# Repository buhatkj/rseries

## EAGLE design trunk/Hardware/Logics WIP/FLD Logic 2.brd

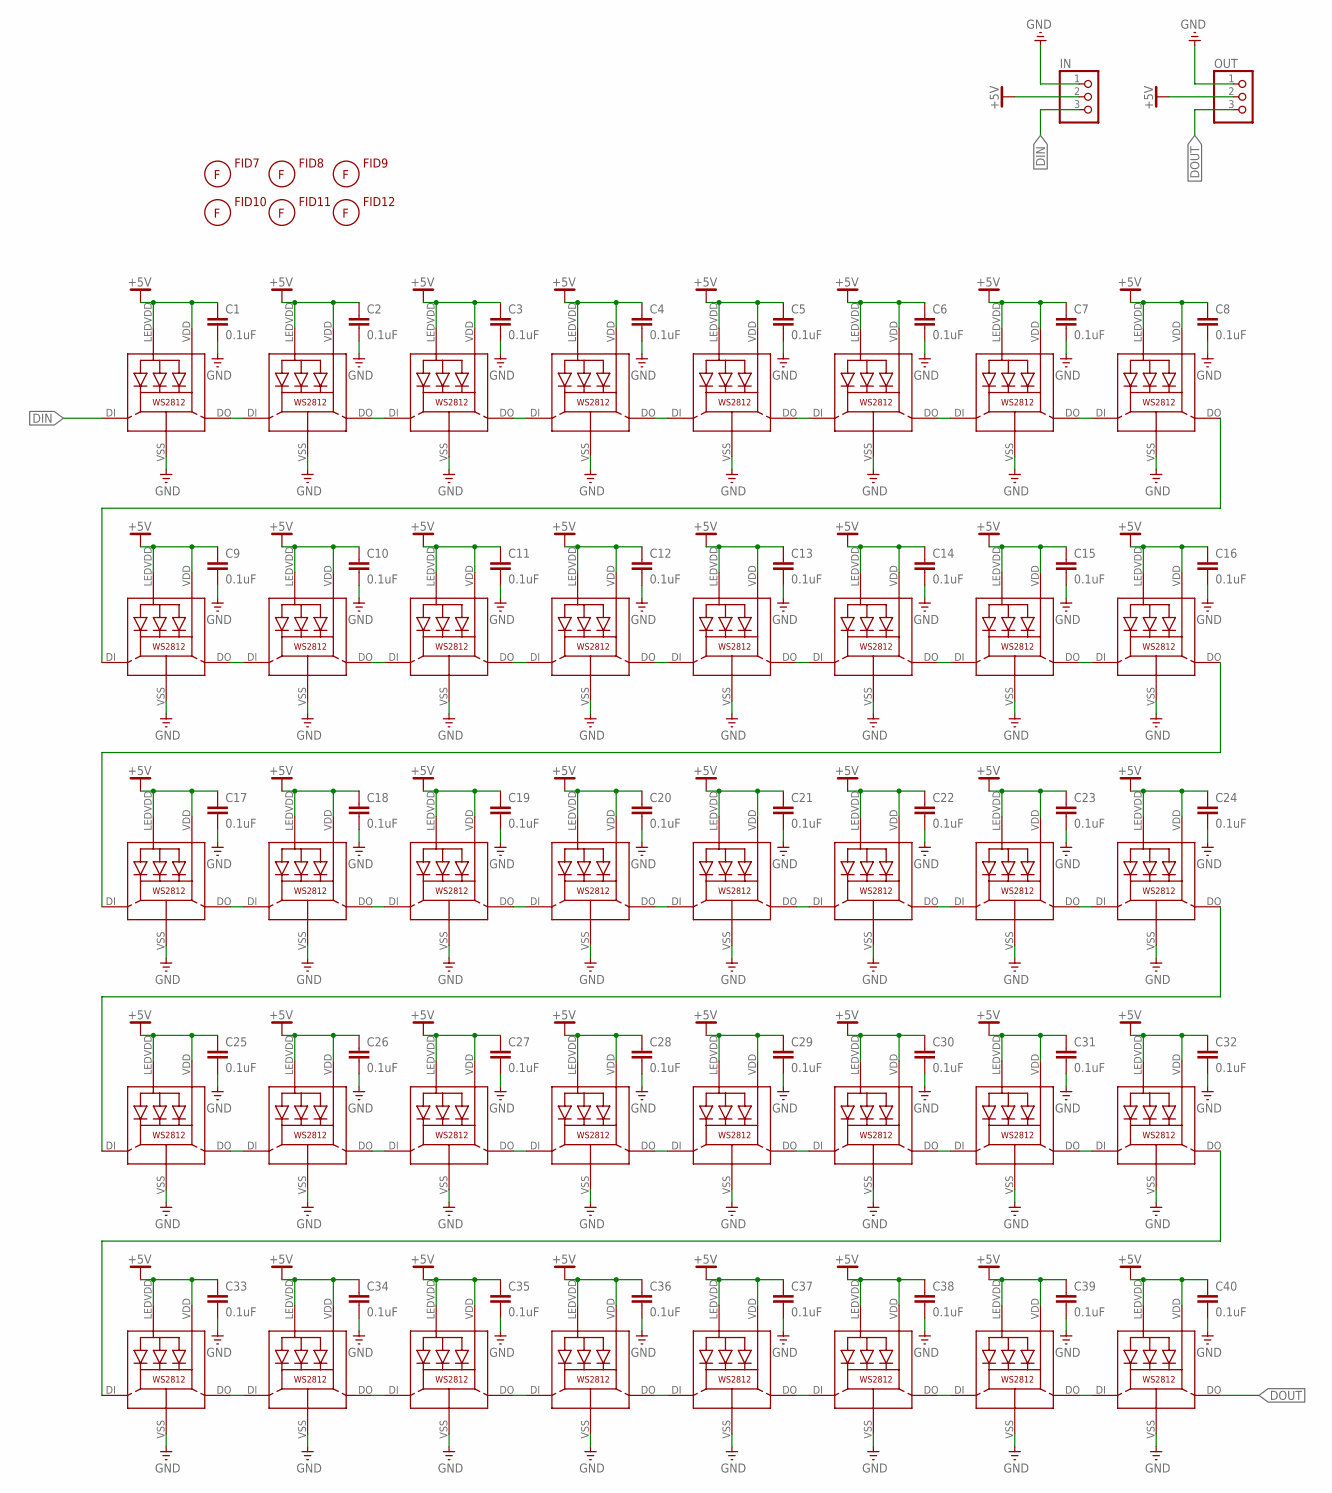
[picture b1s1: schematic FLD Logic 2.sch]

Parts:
C1, C2, C3, C4, C5, C6, C7, C8, C9, C10, C11, C12, C13, C14, C15, C16, C17, C18, C19, C20, C21, C22, C23, C24, C25, C26, C27, C28, C29, C30, C31, C32, C33, C34, C35, C36, C37, C38, C39, C40: 0.1uF; 0805
FID7, FID8, FID9, FID10, FID11, FID12: FIDUCIAL; FIDUCIAL_G15
IN: PINHD-1X3; 1X03
LED1, LED2, LED3, LED4, LED5, LED6, LED7, LED8, LED9, LED10, LED11, LED12, LED13, LED14, LED15, LED16, LED17, LED18, LED19, LED20, LED21, LED22, LED23, LED24, LED25, LED26, LED27, LED28, LED29, LED30, LED31, LED32, LED33, LED34, LED35, LED36, LED37, LED38, LED39, LED40: WS2812
OUT: PINHD-1X3; 1X03

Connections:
+5V: C1.1, C2.1, C3.1, C4.1, C5.1, C6.1, C7.1, C8.1, C9.1, C10.1, C11.1, C12.1, C13.1, C14.1, C15.1, C16.1, C17.1, C18.1, C19.1, C20.1, C21.1, C22.1, C23.1, C24.1, C25.1, C26.1, C27.1, C28.1, C29.1, C30.1, C31.1, C32.1, C33.1, C34.1, C35.1, C36.1, C37.1, C38.1, C39.1, C40.1, IN.2, LED1.LEDVDD, LED1.VDD, LED2.LEDVDD, LED2.VDD, LED3.LEDVDD, LED3.VDD, LED4.LEDVDD, LED4.VDD, LED5.LEDVDD, LED5.VDD, LED6.LEDVDD, LED6.VDD, LED7.LEDVDD, LED7.VDD, LED8.LEDVDD, LED8.VDD, LED9.LEDVDD, LED9.VDD, LED10.LEDVDD, LED10.VDD, LED11.LEDVDD, LED11.VDD, LED12.LEDVDD, LED12.VDD, LED13.LEDVDD, LED13.VDD, LED14.LEDVDD, LED14.VDD, LED15.LEDVDD, LED15.VDD, LED16.LEDVDD, LED16.VDD, LED17.LEDVDD, LED17.VDD, LED18.LEDVDD, LED18.VDD, LED19.LEDVDD, LED19.VDD, LED20.LEDVDD, LED20.VDD, LED21.LEDVDD, LED21.VDD, LED22.LEDVDD, LED22.VDD, LED23.LEDVDD, LED23.VDD, LED24.LEDVDD, LED24.VDD, LED25.LEDVDD, LED25.VDD, LED26.LEDVDD, LED26.VDD, LED27.LEDVDD, LED27.VDD, LED28.LEDVDD, LED28.VDD, LED29.LEDVDD, LED29.VDD, LED30.LEDVDD, LED30.VDD, LED31.LEDVDD, LED31.VDD, LED32.LEDVDD, LED32.VDD, LED33.LEDVDD, LED33.VDD, LED34.LEDVDD, LED34.VDD, LED35.LEDVDD, LED35.VDD, LED36.LEDVDD, LED36.VDD, LED37.LEDVDD, LED37.VDD, LED38.LEDVDD, LED38.VDD, LED39.LEDVDD, LED39.VDD, LED40.LEDVDD, LED40.VDD, OUT.2
DIN: IN.3, LED1.DI
DOUT: LED40.DO, OUT.3
GND: C1.2, C2.2, C3.2, C4.2, C5.2, C6.2, C7.2, C8.2, C9.2, C10.2, C11.2, C12.2, C13.2, C14.2, C15.2, C16.2, C17.2, C18.2, C19.2, C20.2, C21.2, C22.2, C23.2, C24.2, C25.2, C26.2, C27.2, C28.2, C29.2, C30.2, C31.2, C32.2, C33.2, C34.2, C35.2, C36.2, C37.2, C38.2, C39.2, C40.2, IN.1, LED1.VSS (GND), LED2.VSS (GND), LED3.VSS (GND), LED4.VSS (GND), LED5.VSS (GND), LED6.VSS (GND), LED7.VSS (GND), LED8.VSS (GND), LED9.VSS (GND), LED10.VSS (GND), LED11.VSS (GND), LED12.VSS (GND), LED13.VSS (GND), LED14.VSS (GND), LED15.VSS (GND), LED16.VSS (GND), LED17.VSS (GND), LED18.VSS (GND), LED19.VSS (GND), LED20.VSS (GND), LED21.VSS (GND), LED22.VSS (GND), LED23.VSS (GND), LED24.VSS (GND), LED25.VSS (GND), LED26.VSS (GND), LED27.VSS (GND), LED28.VSS (GND), LED29.VSS (GND), LED30.VSS (GND), LED31.VSS (GND), LED32.VSS (GND), LED33.VSS (GND), LED34.VSS (GND), LED35.VSS (GND), LED36.VSS (GND), LED37.VSS (GND), LED38.VSS (GND), LED39.VSS (GND), LED40.VSS (GND), OUT.1
unnamed: LED1.DO, LED2.DI
unnamed: LED3.DO, LED4.DI
unnamed: LED2.DO, LED3.DI
unnamed: LED5.DO, LED6.DI
unnamed: LED7.DO, LED8.DI
unnamed: LED6.DO, LED7.DI
unnamed: LED4.DO, LED5.DI
unnamed: LED9.DO, LED10.DI
unnamed: LED11.DO, LED12.DI
unnamed: LED10.DO, LED11.DI
unnamed: LED13.DO, LED14.DI
unnamed: LED15.DO, LED16.DI
unnamed: LED14.DO, LED15.DI
unnamed: LED12.DO, LED13.DI
unnamed: LED17.DO, LED18.DI
unnamed: LED19.DO, LED20.DI
unnamed: LED18.DO, LED19.DI
unnamed: LED21.DO, LED22.DI
unnamed: LED23.DO, LED24.DI
unnamed: LED22.DO, LED23.DI
unnamed: LED20.DO, LED21.DI
unnamed: LED25.DO, LED26.DI
unnamed: LED27.DO, LED28.DI
unnamed: LED26.DO, LED27.DI
unnamed: LED29.DO, LED30.DI
unnamed: LED31.DO, LED32.DI
unnamed: LED30.DO, LED31.DI
unnamed: LED28.DO, LED29.DI
unnamed: LED8.DO, LED9.DI
unnamed: LED16.DO, LED17.DI
unnamed: LED24.DO, LED25.DI
unnamed: LED33.DO, LED34.DI
unnamed: LED35.DO, LED36.DI
unnamed: LED34.DO, LED35.DI
unnamed: LED37.DO, LED38.DI
unnamed: LED39.DO, LED40.DI
unnamed: LED38.DO, LED39.DI
unnamed: LED36.DO, LED37.DI
unnamed: LED32.DO, LED33.DI

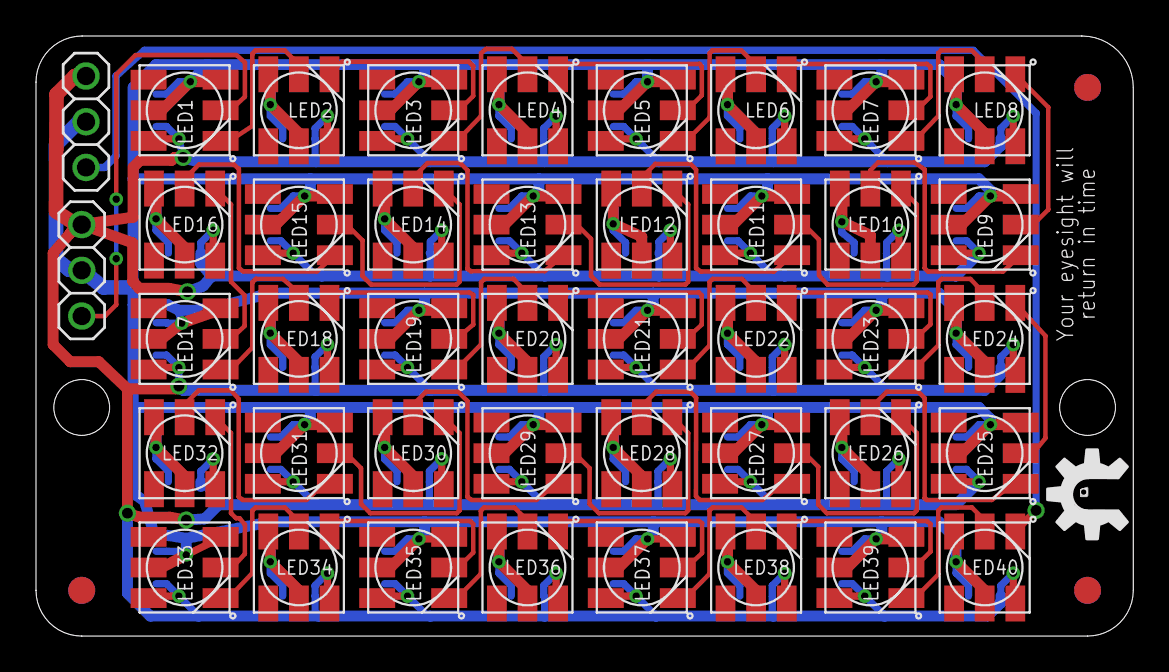
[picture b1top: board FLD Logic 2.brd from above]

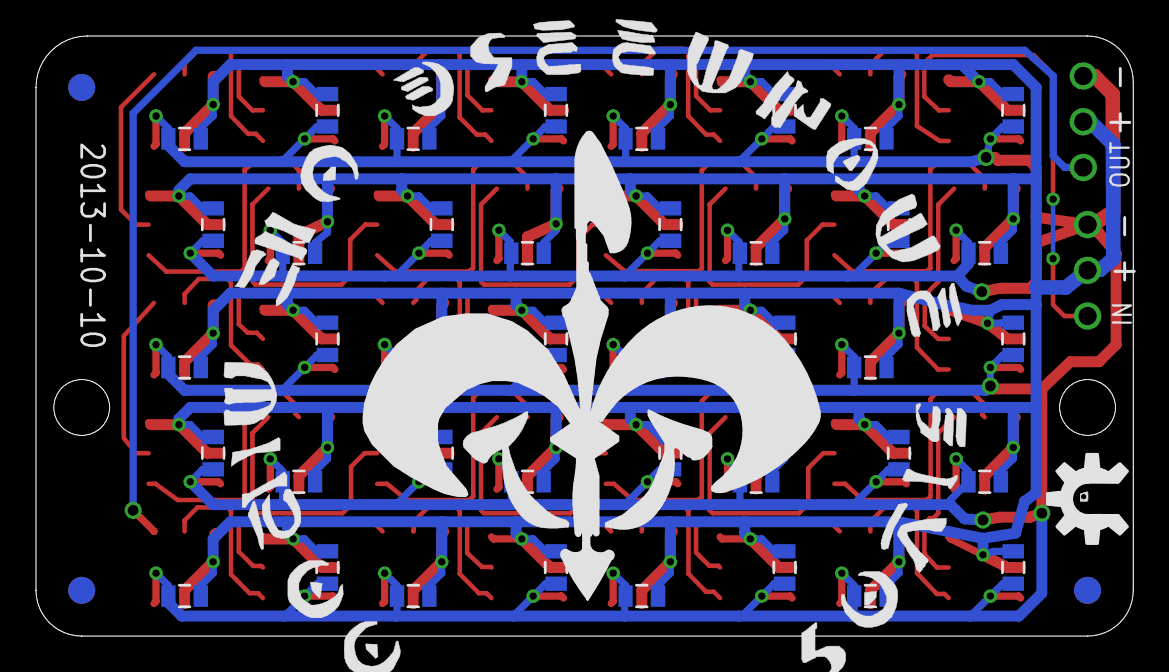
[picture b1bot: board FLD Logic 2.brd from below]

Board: 2 copper layers, 61.0 x 33.3 mm, 91 parts (44 on the bottom side), 43 nets.

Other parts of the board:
U$1: ROYAL-ENGINEERS-OF-NABOO-BOTTOM-LARGE
U$2, U$3: RSERIES-OSHW-LOGO-MEDIUM-BOTTOM

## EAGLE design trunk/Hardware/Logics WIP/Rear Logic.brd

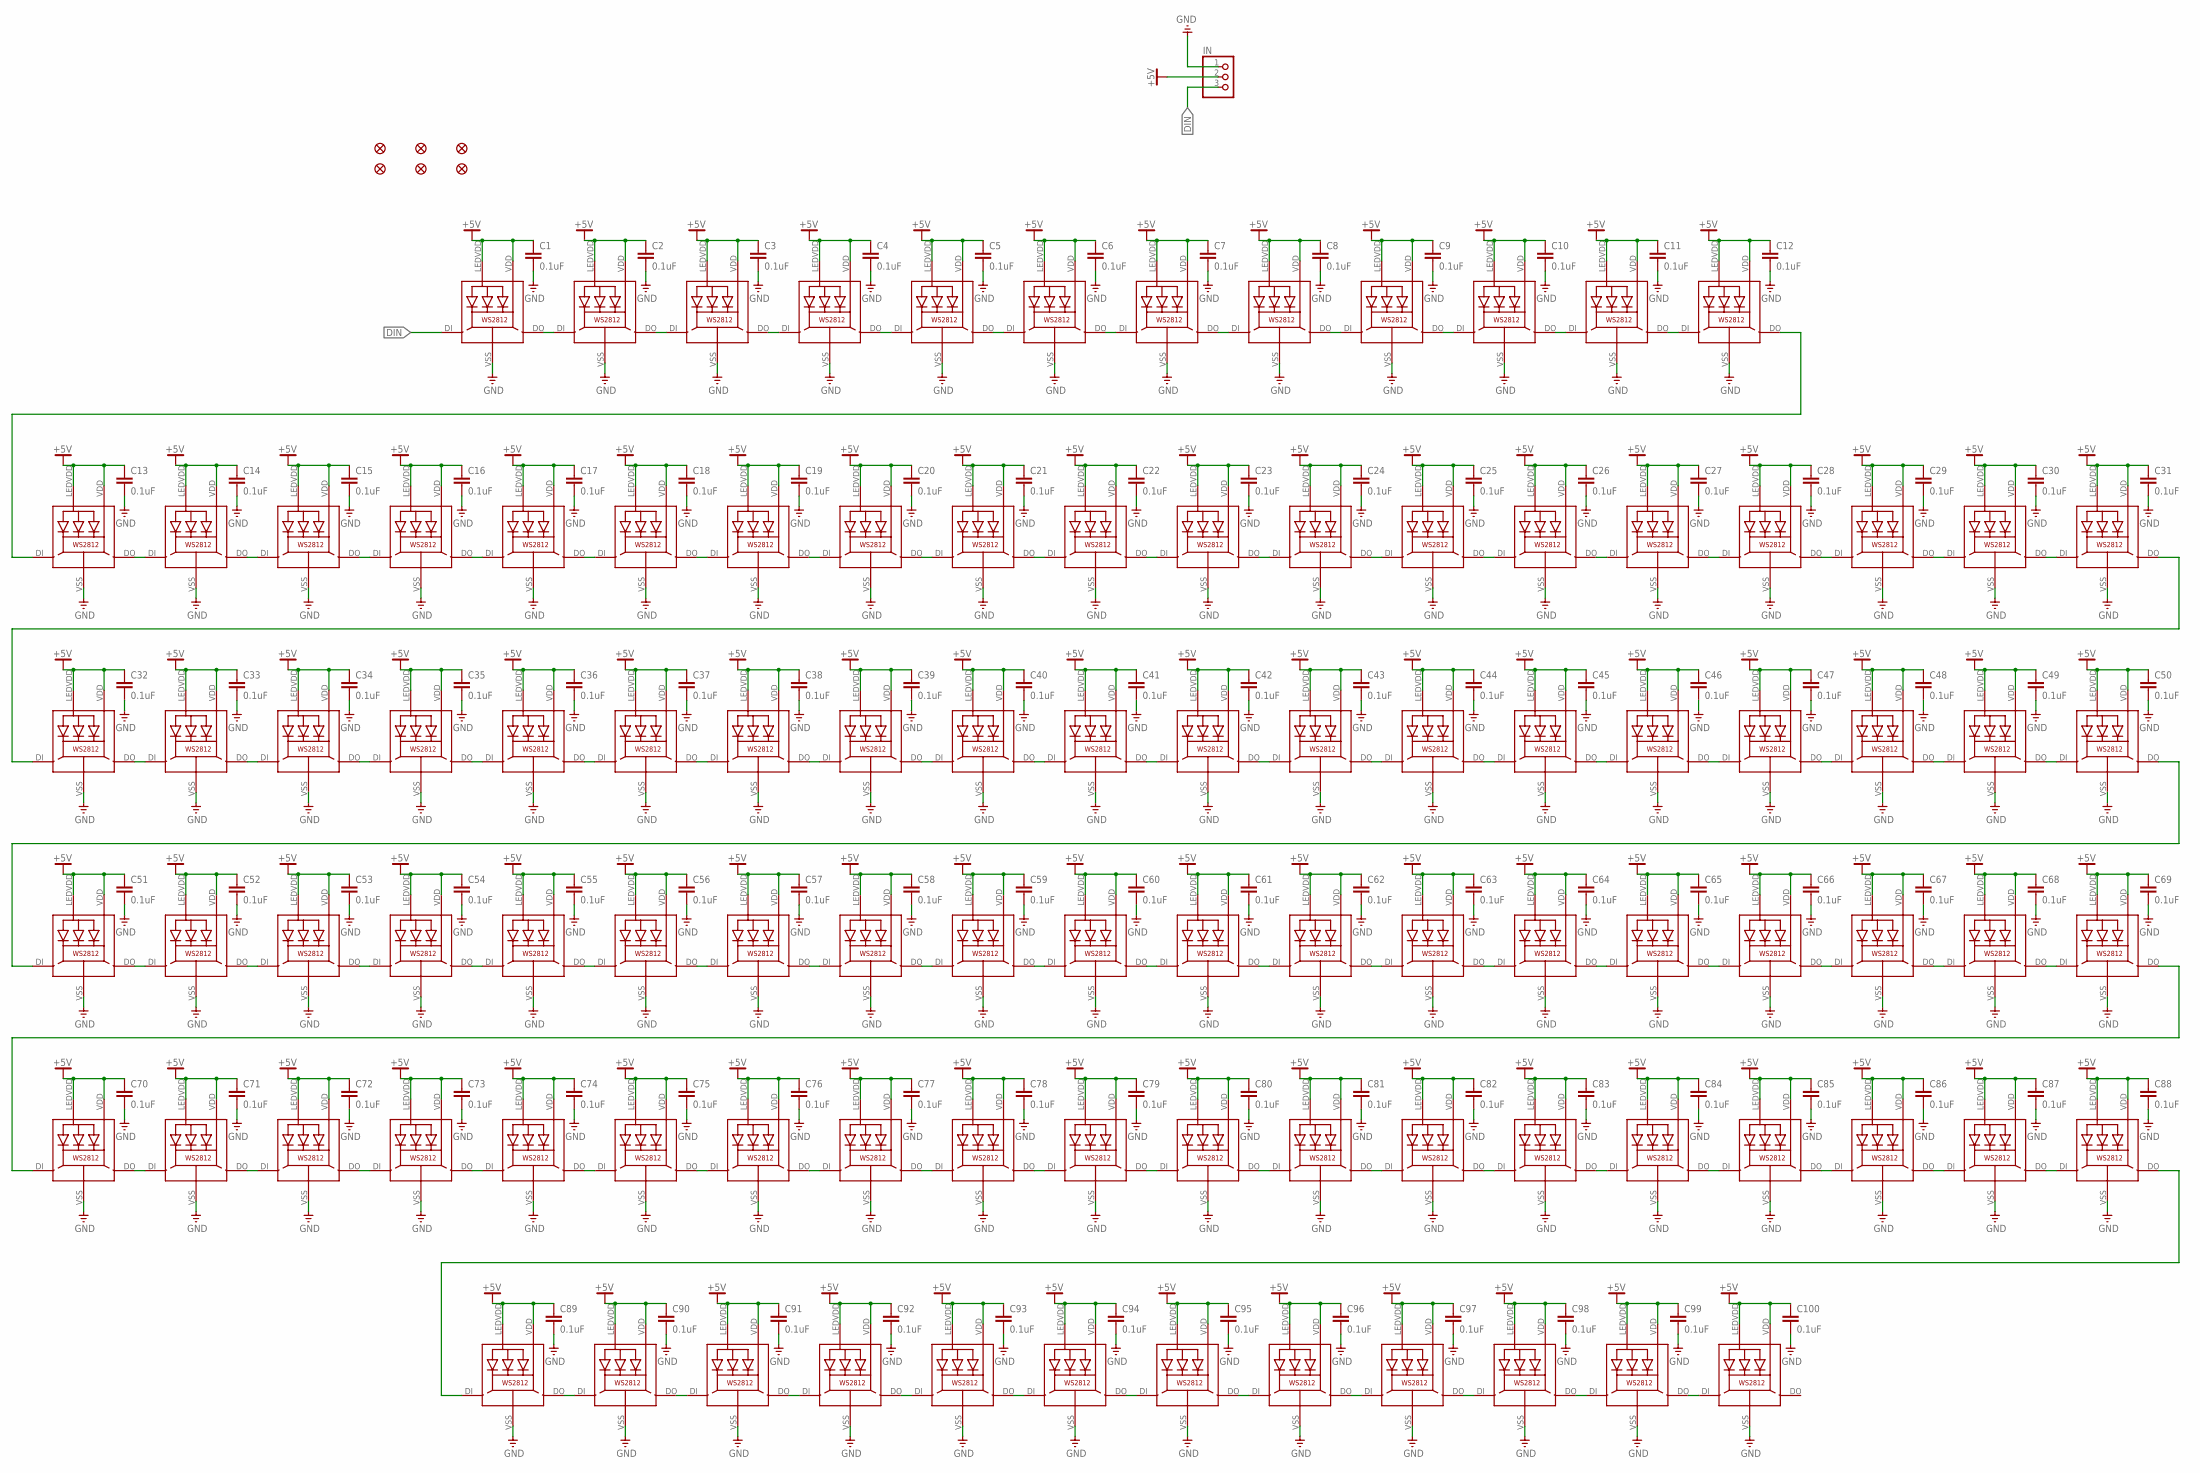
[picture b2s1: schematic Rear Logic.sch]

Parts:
C1, C2, C3, C4, C5, C6, C7, C8, C9, C10, C11, C12, C13, C14, C15, C16, C17, C18, C19, C20, C21, C22, C23, C24, C25, C26, C27, C28, C29, C30, C31, C32, C33, C34, C35, C36, C37, C38, C39, C40, C41, C42, C43, C44, C45, C46, C47, C48, C49, C50, C51, C52, C53, C54, C55, C56, C57, C58, C59, C60, C61, C62, C63, C64, C65, C66, C67, C68, C69, C70, C71, C72, C73, C74, C75, C76, C77, C78, C79, C80, C81, C82, C83, C84, C85, C86, C87, C88, C89, C90, C91, C92, C93, C94, C95, C96, C97, C98, C99, C100: 0.1uF; 0805
FID1, FID2, FID3, FID4, FID5, FID6: FIDUCIAL1.5X3; FIDUCIAL-1.5X3
IN: PINHD-1X3; 1X03
LED1, LED2, LED3, LED4, LED5, LED6, LED7, LED8, LED9, LED10, LED11, LED12, LED13, LED14, LED15, LED16, LED17, LED18, LED19, LED20, LED21, LED22, LED23, LED24, LED25, LED26, LED27, LED28, LED29, LED30, LED31, LED32, LED33, LED34, LED35, LED36, LED37, LED38, LED39, LED40, LED41, LED42, LED43, LED44, LED45, LED46, LED47, LED48, LED49, LED50, LED51, LED52, LED53, LED54, LED55, LED56, LED57, LED58, LED59, LED60, LED61, LED62, LED63, LED64, LED65, LED66, LED67, LED68, LED69, LED70, LED71, LED72, LED73, LED74, LED75, LED76, LED77, LED78, LED79, LED80, LED81, LED82, LED83, LED84, LED85, LED86, LED87, LED88, LED89, LED90, LED91, LED92, LED93, LED94, LED95, LED96, LED97, LED98, LED99, LED100: WS2812

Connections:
+5V: C1.1, C2.1, C3.1, C4.1, C5.1, C6.1, C7.1, C8.1, C9.1, C10.1, C11.1, C12.1, C13.1, C14.1, C15.1, C16.1, C17.1, C18.1, C19.1, C20.1, C21.1, C22.1, C23.1, C24.1, C25.1, C26.1, C27.1, C28.1, C29.1, C30.1, C31.1, C32.1, C33.1, C34.1, C35.1, C36.1, C37.1, C38.1, C39.1, C40.1, C41.1, C42.1, C43.1, C44.1, C45.1, C46.1, C47.1, C48.1, C49.1, C50.1, C51.1, C52.1, C53.1, C54.1, C55.1, C56.1, C57.1, C58.1, C59.1, C60.1, C61.1, C62.1, C63.1, C64.1, C65.1, C66.1, C67.1, C68.1, C69.1, C70.1, C71.1, C72.1, C73.1, C74.1, C75.1, C76.1, C77.1, C78.1, C79.1, C80.1, C81.1, C82.1, C83.1, C84.1, C85.1, C86.1, C87.1, C88.1, C89.1, C90.1, C91.1, C92.1, C93.1, C94.1, C95.1, C96.1, C97.1, C98.1, C99.1, C100.1, IN.2, LED1.LEDVDD, LED1.VDD, LED2.LEDVDD, LED2.VDD, LED3.LEDVDD, LED3.VDD, LED4.LEDVDD, LED4.VDD, LED5.LEDVDD, LED5.VDD, LED6.LEDVDD, LED6.VDD, LED7.LEDVDD, LED7.VDD, LED8.LEDVDD, LED8.VDD, LED9.LEDVDD, LED9.VDD, LED10.LEDVDD, LED10.VDD, LED11.LEDVDD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
DIN: IN.3, LED1.DI
GND: C1.2, C2.2, C3.2, C4.2, C5.2, C6.2, C7.2, C8.2, C9.2, C10.2, C11.2, C12.2, C13.2, C14.2, C15.2, C16.2, C17.2, C18.2, C19.2, C20.2, C21.2, C22.2, C23.2, C24.2, C25.2, C26.2, C27.2, C28.2, C29.2, C30.2, C31.2, C32.2, C33.2, C34.2, C35.2, C36.2, C37.2, C38.2, C39.2, C40.2, C41.2, C42.2, C43.2, C44.2, C45.2, C46.2, C47.2, C48.2, C49.2, C50.2, C51.2, C52.2, C53.2, C54.2, C55.2, C56.2, C57.2, C58.2, C59.2, C60.2, C61.2, C62.2, C63.2, C64.2, C65.2, C66.2, C67.2, C68.2, C69.2, C70.2, C71.2, C72.2, C73.2, C74.2, C75.2, C76.2, C77.2, C78.2, C79.2, C80.2, C81.2, C82.2, C83.2, C84.2, C85.2, C86.2, C87.2, C88.2, C89.2, C90.2, C91.2, C92.2, C93.2, C94.2, C95.2, C96.2, C97.2, C98.2, C99.2, C100.2, IN.1, LED1.VSS (GND), LED2.VSS (GND), LED3.VSS (GND), LED4.VSS (GND), LED5.VSS (GND), LED6.VSS (GND), LED7.VSS (GND), LED8.VSS (GND), LED9.VSS (GND), LED10.VSS (GND), LED11.VSS (GND), LED12.VSS (GND), LED13.VSS (GND), LED14.VSS (GND), LED15.VSS (GND), LED16.VSS (GND), LED17.VSS (GND), LED18.VSS (GND), LED19.VSS (GND), LED20.VSS (GND), LED21.VSS (GND)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
unnamed: LED1.DO, LED2.DI
unnamed: LED3.DO, LED4.DI
unnamed: LED2.DO, LED3.DI
unnamed: LED5.DO, LED6.DI
unnamed: LED7.DO, LED8.DI
unnamed: LED6.DO, LED7.DI
unnamed: LED4.DO, LED5.DI
unnamed: LED9.DO, LED10.DI
unnamed: LED11.DO, LED12.DI
unnamed: LED10.DO, LED11.DI
unnamed: LED8.DO, LED9.DI
unnamed: LED13.DO, LED14.DI
unnamed: LED15.DO, LED16.DI
unnamed: LED14.DO, LED15.DI
unnamed: LED17.DO, LED18.DI
unnamed: LED19.DO, LED20.DI
unnamed: LED18.DO, LED19.DI
unnamed: LED16.DO, LED17.DI
unnamed: LED21.DO, LED22.DI
unnamed: LED23.DO, LED24.DI
unnamed: LED22.DO, LED23.DI
unnamed: LED20.DO, LED21.DI
unnamed: LED26.DO, LED27.DI
unnamed: LED25.DO, LED26.DI
unnamed: LED28.DO, LED29.DI
unnamed: LED30.DO, LED31.DI
unnamed: LED29.DO, LED30.DI
unnamed: LED27.DO, LED28.DI
unnamed: LED24.DO, LED25.DI
unnamed: LED32.DO, LED33.DI
unnamed: LED34.DO, LED35.DI
unnamed: LED33.DO, LED34.DI
unnamed: LED36.DO, LED37.DI
unnamed: LED38.DO, LED39.DI
unnamed: LED37.DO, LED38.DI
unnamed: LED35.DO, LED36.DI
unnamed: LED40.DO, LED41.DI
unnamed: LED42.DO, LED43.DI
unnamed: LED41.DO, LED42.DI
unnamed: LED39.DO, LED40.DI
unnamed: LED45.DO, LED46.DI
unnamed: LED44.DO, LED45.DI
unnamed: LED47.DO, LED48.DI
unnamed: LED49.DO, LED50.DI
unnamed: LED48.DO, LED49.DI
unnamed: LED46.DO, LED47.DI
unnamed: LED43.DO, LED44.DI
unnamed: LED51.DO, LED52.DI
unnamed: LED53.DO, LED54.DI
unnamed: LED52.DO, LED53.DI
unnamed: LED55.DO, LED56.DI
unnamed: LED57.DO, LED58.DI
unnamed: LED56.DO, LED57.DI
unnamed: LED54.DO, LED55.DI
unnamed: LED59.DO, LED60.DI
unnamed: LED61.DO, LED62.DI
unnamed: LED60.DO, LED61.DI
unnamed: LED58.DO, LED59.DI
unnamed: LED64.DO, LED65.DI
unnamed: LED63.DO, LED64.DI
unnamed: LED66.DO, LED67.DI
unnamed: LED68.DO, LED69.DI
unnamed: LED67.DO, LED68.DI
unnamed: LED65.DO, LED66.DI
unnamed: LED62.DO, LED63.DI
unnamed: LED70.DO, LED71.DI
unnamed: LED72.DO, LED73.DI
unnamed: LED71.DO, LED72.DI
unnamed: LED74.DO, LED75.DI
unnamed: LED76.DO, LED77.DI
unnamed: LED75.DO, LED76.DI
unnamed: LED73.DO, LED74.DI
unnamed: LED78.DO, LED79.DI
unnamed: LED80.DO, LED81.DI
unnamed: LED79.DO, LED80.DI
unnamed: LED77.DO, LED78.DI
unnamed: LED83.DO, LED84.DI
unnamed: LED82.DO, LED83.DI
unnamed: LED85.DO, LED86.DI
unnamed: LED87.DO, LED88.DI
unnamed: LED86.DO, LED87.DI
unnamed: LED84.DO, LED85.DI
unnamed: LED81.DO, LED82.DI
unnamed: LED89.DO, LED90.DI
unnamed: LED91.DO, LED92.DI
unnamed: LED90.DO, LED91.DI
unnamed: LED93.DO, LED94.DI
unnamed: LED95.DO, LED96.DI
unnamed: LED94.DO, LED95.DI
unnamed: LED92.DO, LED93.DI
unnamed: LED97.DO, LED98.DI
unnamed: LED99.DO, LED100.DI
unnamed: LED98.DO, LED99.DI
unnamed: LED96.DO, LED97.DI
unnamed: LED12.DO, LED13.DI
unnamed: LED31.DO, LED32.DI
unnamed: LED50.DO, LED51.DI
unnamed: LED69.DO, LED70.DI
unnamed: LED88.DO, LED89.DI

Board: 2 copper layers, 207 parts (103 on the bottom side), 102 nets, no tracks yet.

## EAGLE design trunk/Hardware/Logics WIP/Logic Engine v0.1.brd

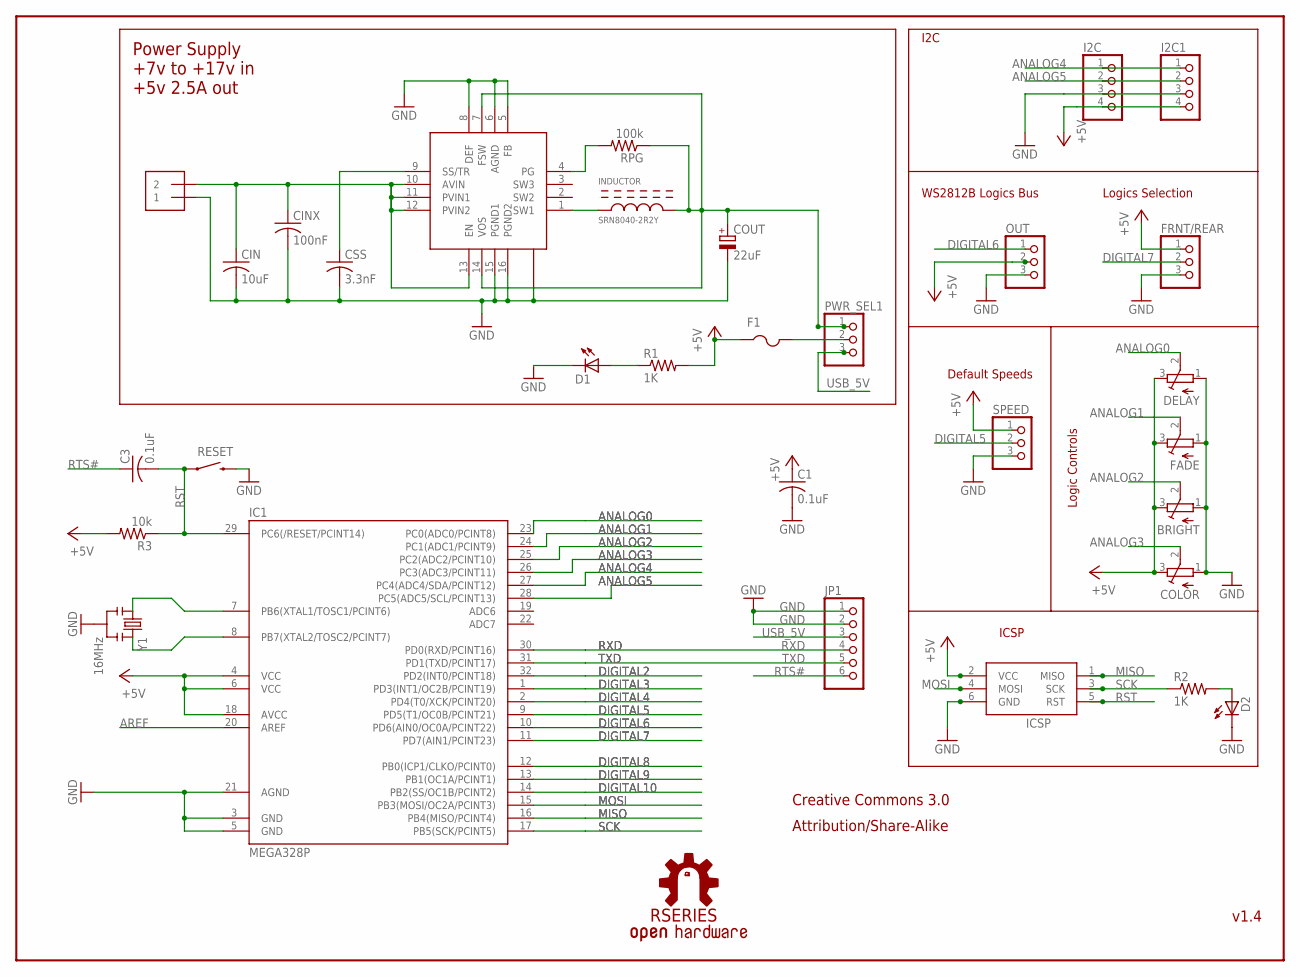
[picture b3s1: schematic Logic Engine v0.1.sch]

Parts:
BRIGHT: TRIMPOT3364W; 3364
C1, C3: 0.1uF; C0805K
CIN: 10uF; C1206
CINX: 100nF; C0805K
COLOR: TRIMPOT3364W; 3364
COUT: 22uF; CASE_B
CSS: 3.3nF; C0805K
D1: LEDCHIPLED_1206; CHIPLED_1206
D2: Green; CHIPLED_1206
DELAY: TRIMPOT3364W; 3364
EXT.PWR: 1X2-3.5MM
F1: PTCFUSE-1812; 1812
FADE: TRIMPOT3364W; 3364
FRNT/REAR: PINHD-1X3; 1X03
I2C, I2C1: PINHD-1X4CB; 1X04-CB
IC1: MEGA328P; TQFP32-08
ICSP: AVRISP-6; AVRISP
INDUCTOR: SRN8040-2R2Y; SRN8040
JP1: PINHD-1X6CLEAN; 1X06-CLEAN
OUT: PINHD-1X3; 1X03
PWR_SEL1: PINHD-1X3; 1X03
R1, R2: 1K; R0805
R3: 10k; R0805
REG: TPS62133; TPS6213X
RESET: SWITCH-MOMENTARY-2SMD; TACTILE_SWITCH_SMD
RPG: 100k; R0805
SPEED: PINHD-1X3; 1X03
U$2: RSERIES-OSHW-LOGOMEDIUM; RSERIES-OSHW-LOGO-MEDIUM
Y1: 16MHz; RESONATOR-SMD

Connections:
+5V: BRIGHT.3 (E), C1.1, COLOR.3 (E), DELAY.3 (E), F1.1, FADE.3 (E), FRNT/REAR.1, I2C.4, I2C1.4, IC1.4 (VCC), IC1.6 (VCC), IC1.18 (AVCC), ICSP.2 (VCC), OUT.2, R1.2, R3.2, SPEED.1; also elsewhere on the board
ANALOG0: DELAY.2 (S), IC1.23 (PC0(ADC0/PCINT8))
ANALOG1: FADE.2 (S), IC1.24 (PC1(ADC1/PCINT9))
ANALOG2: BRIGHT.2 (S), IC1.25 (PC2(ADC2/PCINT10))
ANALOG3: COLOR.2 (S), IC1.26 (PC3(ADC3/PCINT11))
ANALOG4: I2C.1, I2C1.1, IC1.27 (PC4(ADC4/SDA/PCINT12))
ANALOG5: I2C.2, I2C1.2, IC1.28 (PC5(ADC5/SCL/PCINT13))
AREF: IC1.20 (AREF)
DIGITAL2: IC1.32 (PD2(INT0/PCINT18))
DIGITAL3: IC1.1 (PD3(INT1/OC2B/PCINT19))
DIGITAL4: IC1.2 (PD4(T0/XCK/PCINT20))
DIGITAL5: IC1.9 (PD5(T1/OC0B/PCINT21)), SPEED.2
DIGITAL6: IC1.10 (PD6(AIN0/OC0A/PCINT22)), OUT.1
DIGITAL7: FRNT/REAR.2, IC1.11 (PD7(AIN1/PCINT23))
DIGITAL8: IC1.12 (PB0(ICP1/CLKO/PCINT0)); also elsewhere on the board
DIGITAL9: IC1.13 (PB1(OC1A/PCINT1)); also elsewhere on the board
DIGITAL10: IC1.14 (PB2(SS/OC1B/PCINT2)); also elsewhere on the board
GND: BRIGHT.1 (A), C1.2, CIN.2, CINX.2, COLOR.1 (A), COUT.-, CSS.2, D1.C, D2.C, DELAY.1 (A), EXT.PWR.1, FADE.1 (A), FRNT/REAR.3, I2C.3, I2C1.3, IC1.3 (GND), IC1.5 (GND), IC1.21 (AGND), ICSP.6 (GND), JP1.1, JP1.2, OUT.3, REG.5 (FB), REG.6 (AGND), REG.8 (DEF), REG.15 (PGND1), REG.16 (PGND2), REG.17-THERMALPAD (THERM), RESET.3 (2), SPEED.3, Y1.2; also elsewhere on the board
MISO: IC1.16 (PB4(MISO/PCINT4)), ICSP.1 (MISO)
MOSI: IC1.15 (PB3(MOSI/OC2A/PCINT3)), ICSP.4 (MOSI)
unnamed: IC1.7 (PB6(XTAL1/TOSC1/PCINT6)), Y1.1
unnamed: IC1.8 (PB7(XTAL2/TOSC2/PCINT7)), Y1.3
unnamed: INDUCTOR.P$1 (P1), REG.1 (SW1)
unnamed: D2.A, R2.2
unnamed: D1.A, R1.1
unnamed: CSS.1, REG.9 (SS/TR)
unnamed: REG.4 (PG), RPG.2
unnamed: COUT.+, INDUCTOR.P$2 (P2), PWR_SEL1.1, REG.7 (FSW), REG.14 (VOS), RPG.1
unnamed: F1.2, PWR_SEL1.2
RST: C3.2, IC1.29 (PC6(/RESET/PCINT14)), ICSP.5 (RST), R3.1, RESET.1
RTS#: C3.1, JP1.6
RXD: IC1.30 (PD0(RXD/PCINT16)), JP1.4
SCK: IC1.17 (PB5(SCK/PCINT5)), ICSP.3 (SCK), R2.1
TXD: IC1.31 (PD1(TXD/PCINT17)), JP1.5
USB_5V: JP1.3, PWR_SEL1.3

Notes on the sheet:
v1.4
Creative Commons 3.0
Attribution/Share-Alike
WS2812B Logics Bus
I2C
ICSP
Power Supply +7v to +17v in +5v 2.5A out
Logic Controls
Logics Selection
Default Speeds

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
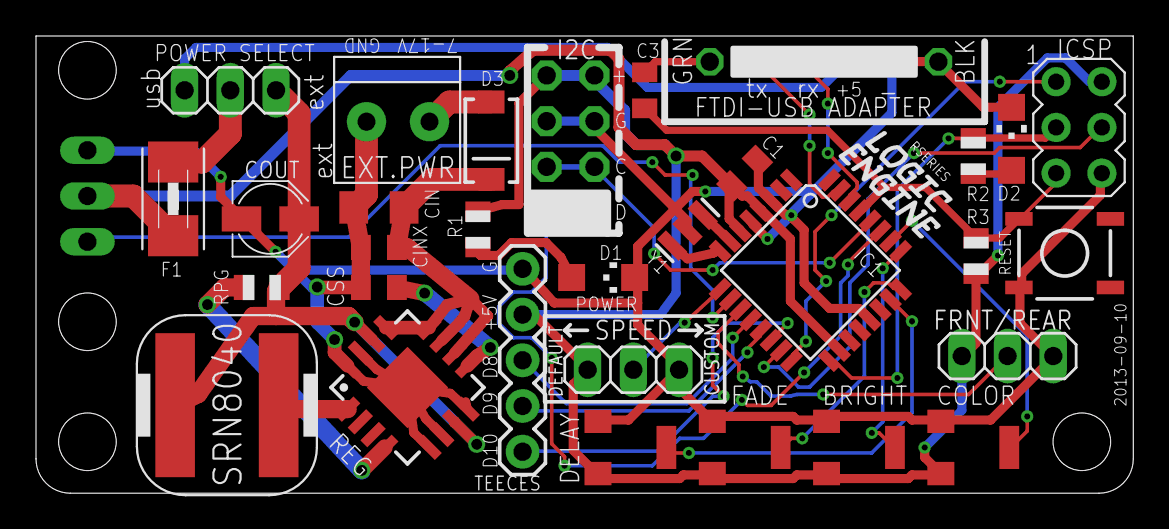
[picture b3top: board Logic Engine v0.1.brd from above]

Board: 2 copper layers, 61.0 x 25.4 mm, 33 parts (1 on the bottom side), 33 nets.

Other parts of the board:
D3: BA340LA; SMA-DIODE
TEECES: 1X05

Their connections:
+5V: TEECES.2; also elsewhere on the board
DIGITAL8: TEECES.3; also elsewhere on the board
DIGITAL9: TEECES.4; also elsewhere on the board
DIGITAL10: TEECES.5; also elsewhere on the board
GND: TEECES.1; also elsewhere on the board

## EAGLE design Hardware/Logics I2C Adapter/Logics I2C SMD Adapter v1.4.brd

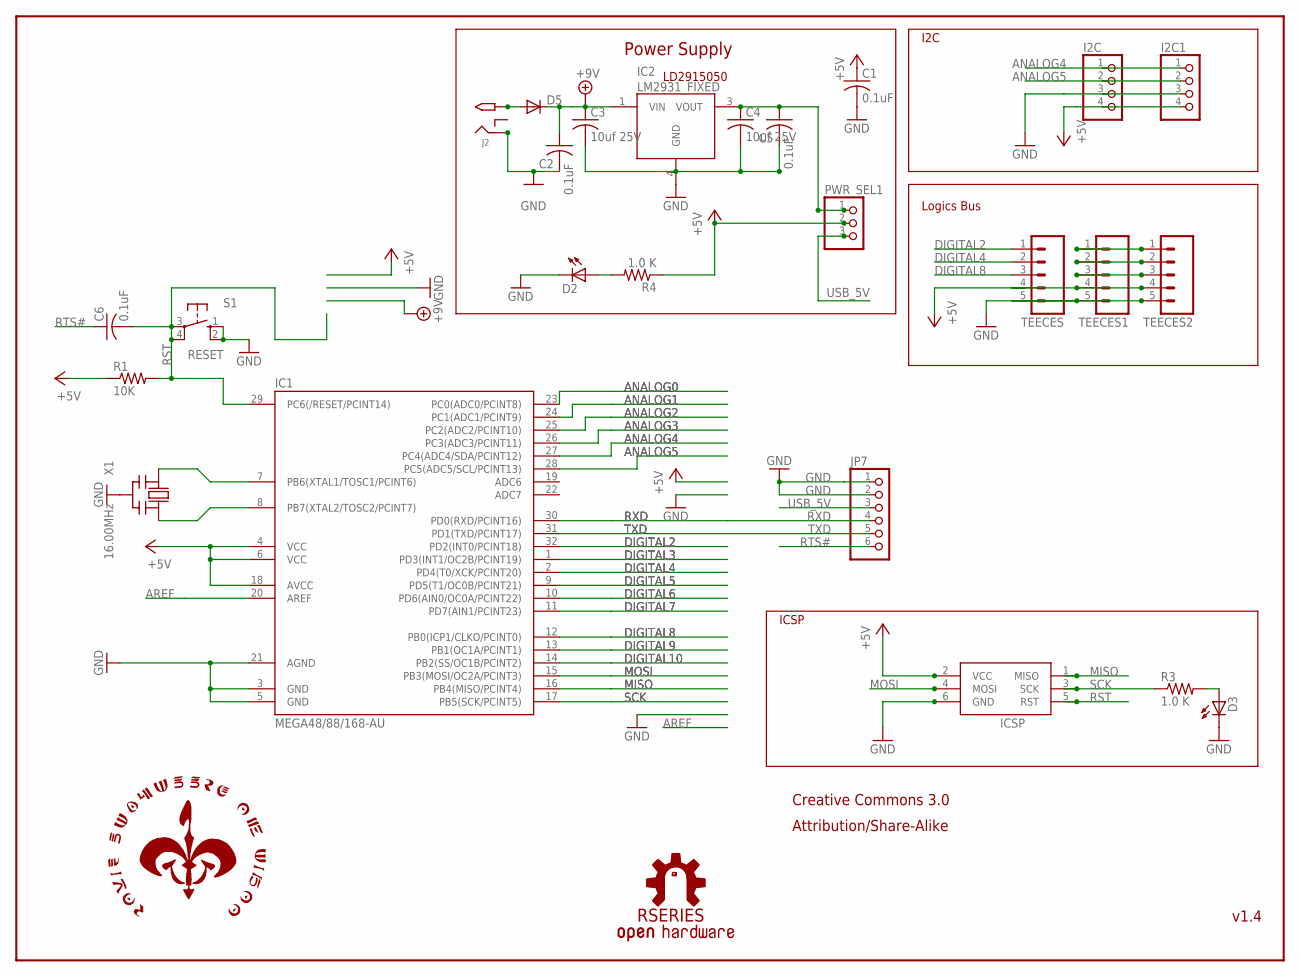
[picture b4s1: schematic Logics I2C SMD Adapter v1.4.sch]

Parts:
C1, C2, C5, C6: 0.1uF; C1206K
C3, C4: 10uf 25V; C1206K
D2: LEDCHIPLED_1206; CHIPLED_1206
D3: Green; CHIPLED_1206
D5: DIODE-SMB; SMB
I2C, I2C1: PINHD-1X4CB; 1X04-CB
IC1: MEGA48/88/168-AU; TQFP32-08
IC2: LM2931_FIXED; DPAK
ICSP: AVRISP-6; AVRISP
J2: 2.1MMJACK; PJ-102A
JP7: PINHD-1X6CLEAN; 1X06-CLEAN
PWR_SEL1: PINHD-1X3; 1X03
R1: 10K; R1206
R3, R4: 1.0 K; M1206
S1: RESET; B3F-10XX
TEECES, TEECES1, TEECES2: M05PTH; 1X05
U$1: ROYAL-ENGINEERS-OF-NABOOSMALL; ROYAL-ENGINEERS-OF-NABOO-SMALL
U$2: RSERIES-OSHW-LOGOMEDIUM; RSERIES-OSHW-LOGO-MEDIUM
X1: 16.00MHz; CERM_OSC

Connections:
+5V: C1.1, I2C.4, I2C1.4, IC1.4 (VCC), IC1.6 (VCC), IC1.18 (AVCC), ICSP.2 (VCC), PWR_SEL1.2, R1.1, R4.1, TEECES.4, TEECES1.4, TEECES2.4
+9V: C2.1, C3.1, D5.C, IC2.1 (VIN)
ANALOG0: IC1.23 (PC0(ADC0/PCINT8))
ANALOG1: IC1.24 (PC1(ADC1/PCINT9))
ANALOG2: IC1.25 (PC2(ADC2/PCINT10))
ANALOG3: IC1.26 (PC3(ADC3/PCINT11))
ANALOG4: I2C.1, I2C1.1, IC1.27 (PC4(ADC4/SDA/PCINT12))
ANALOG5: I2C.2, I2C1.2, IC1.28 (PC5(ADC5/SCL/PCINT13))
AREF: IC1.20 (AREF)
DIGITAL2: IC1.32 (PD2(INT0/PCINT18)), TEECES.1
DIGITAL3: IC1.1 (PD3(INT1/OC2B/PCINT19))
DIGITAL4: IC1.2 (PD4(T0/XCK/PCINT20)), TEECES.2
DIGITAL5: IC1.9 (PD5(T1/OC0B/PCINT21))
DIGITAL6: IC1.10 (PD6(AIN0/OC0A/PCINT22))
DIGITAL7: IC1.11 (PD7(AIN1/PCINT23))
DIGITAL8: IC1.12 (PB0(ICP1/CLKO/PCINT0)), TEECES.3
DIGITAL9: IC1.13 (PB1(OC1A/PCINT1))
DIGITAL10: IC1.14 (PB2(SS/OC1B/PCINT2))
GND: C1.2, C2.2, D2.C, D3.C, I2C.3, I2C1.3, IC1.3 (GND), IC1.5 (GND), IC1.21 (AGND), IC2.4 (GND), ICSP.6 (GND), J2.RING, JP7.1, JP7.2, S1.1 (S), S1.2 (S1), TEECES.5, TEECES1.5, TEECES2.5, X1.P$2 (GND)
MISO: IC1.16 (PB4(MISO/PCINT4)), ICSP.1 (MISO)
MOSI: IC1.15 (PB3(MOSI/OC2A/PCINT3)), ICSP.4 (MOSI)
unnamed: IC1.7 (PB6(XTAL1/TOSC1/PCINT6)), X1.P$1 (IN)
unnamed: IC1.8 (PB7(XTAL2/TOSC2/PCINT7)), X1.P$3 (OUT)
unnamed: TEECES1.3, TEECES2.3
unnamed: D3.A, R3.2
unnamed: D2.A, R4.2
unnamed: D5.A, J2.TIP
unnamed: TEECES1.2, TEECES2.2
unnamed: C3.2, C4.2, C5.2
unnamed: C4.1, C5.1, IC2.3 (VOUT), PWR_SEL1.1
unnamed: TEECES1.1, TEECES2.1
RST: C6.2, IC1.29 (PC6(/RESET/PCINT14)), ICSP.5 (RST), R1.2, S1.3, S1.4 (P1)
RTS#: C6.1, JP7.6
RXD: IC1.30 (PD0(RXD/PCINT16)), JP7.4
SCK: IC1.17 (PB5(SCK/PCINT5)), ICSP.3 (SCK), R3.1
TXD: IC1.31 (PD1(TXD/PCINT17)), JP7.5
USB_5V: JP7.3, PWR_SEL1.3

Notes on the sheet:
v1.4
Creative Commons 3.0
Attribution/Share-Alike
Logics Bus
I2C
ICSP
Power Supply
LD2915050

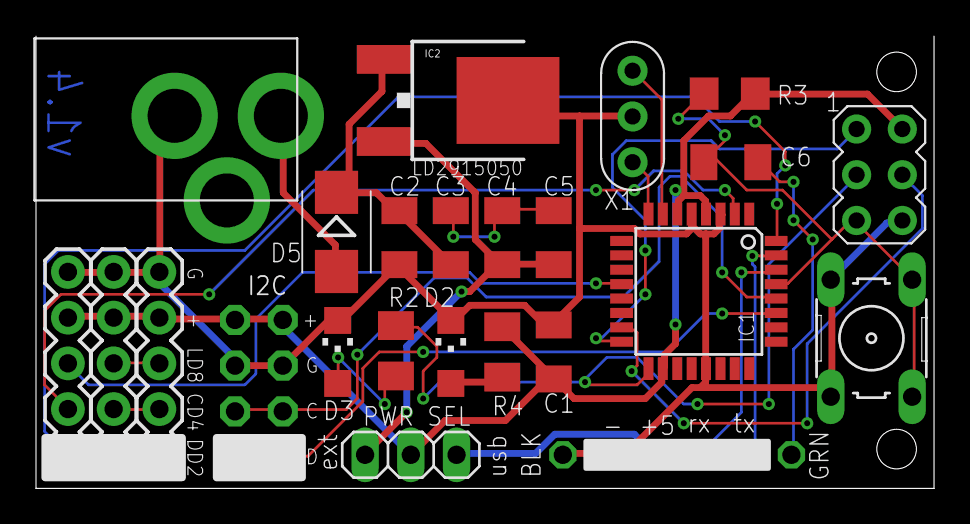
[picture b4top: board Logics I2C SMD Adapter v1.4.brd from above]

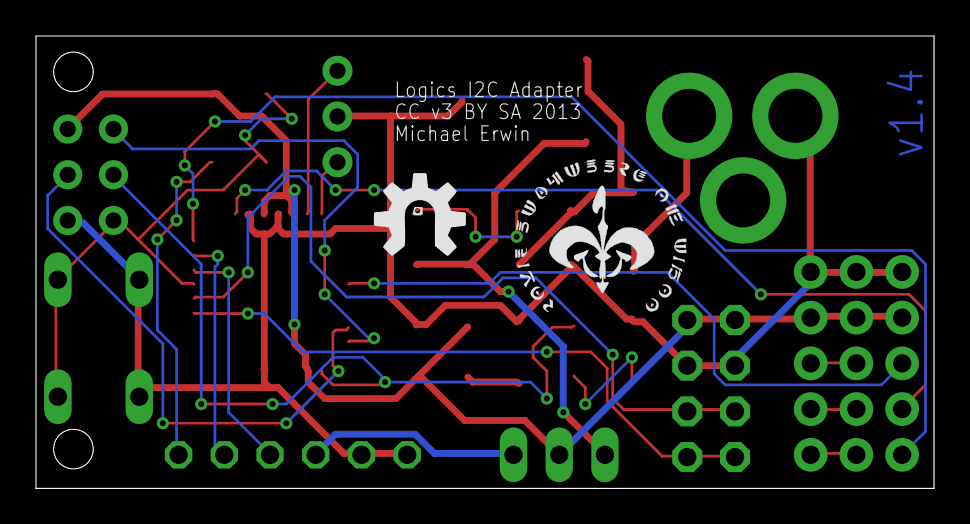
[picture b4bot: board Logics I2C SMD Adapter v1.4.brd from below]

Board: 2 copper layers, 49.9 x 25.1 mm, 27 parts (2 on the bottom side), 26 nets.

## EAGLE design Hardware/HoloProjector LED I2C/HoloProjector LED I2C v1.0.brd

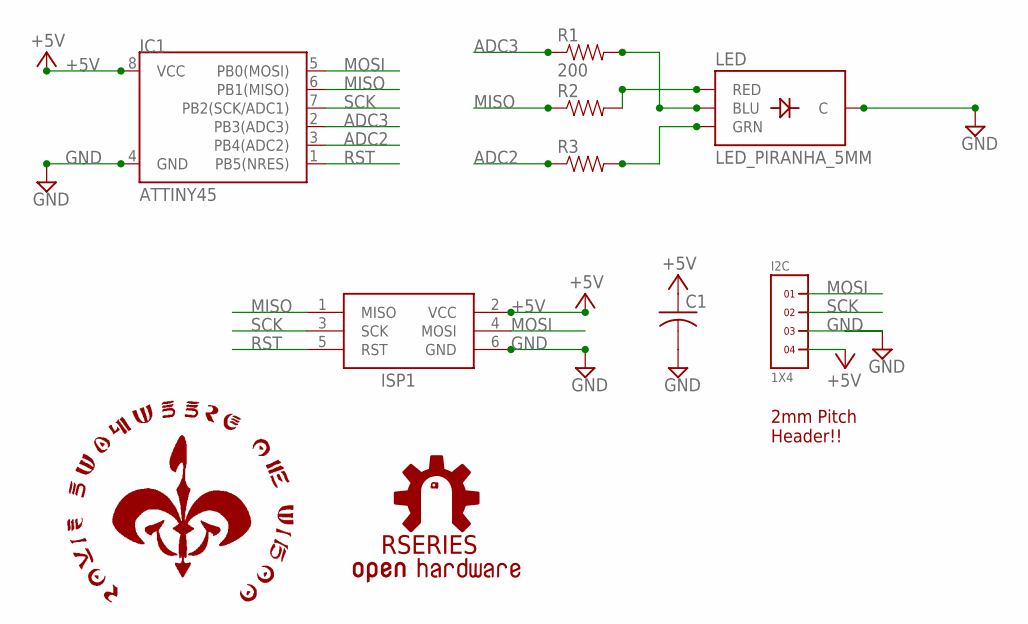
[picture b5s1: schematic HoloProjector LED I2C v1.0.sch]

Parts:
C1: C-USC1206K; C1206K
I2C: 1X4
IC1: ATTINY45; SO08-EIAJ
ISP1: AVRISP-6; AVRISP
LED: LED_PIRANHA_5MM
R1: 200; 1206
R2, R3: RESISTOR1206; 1206
U$1: ROYAL-ENGINEERS-OF-NABOOSMALL; ROYAL-ENGINEERS-OF-NABOO-SMALL
U$2: RSERIES-OSHW-LOGOMEDIUM; RSERIES-OSHW-LOGO-MEDIUM

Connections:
+5V: C1.1, I2C.4, IC1.8 (VCC), ISP1.2 (VCC)
ADC2: IC1.3 (PB4(ADC2)), R3.1
ADC3: IC1.2 (PB3(ADC3)), R1.1
GND: C1.2, I2C.3, IC1.4 (GND), ISP1.6 (GND), LED.- (C)
MISO: IC1.6 (PB1(MISO)), ISP1.1 (MISO), R2.1
MOSI: I2C.1, IC1.5 (PB0(MOSI)), ISP1.4 (MOSI)
unnamed: LED.B (BLU), R1.2
unnamed: LED.R (RED), R2.2
unnamed: LED.G (GRN), R3.2
RST: IC1.1 (PB5(NRES)), ISP1.5 (RST)
SCK: I2C.2, IC1.7 (PB2(SCK/ADC1)), ISP1.3 (SCK)

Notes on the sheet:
2mm Pitch Header!!

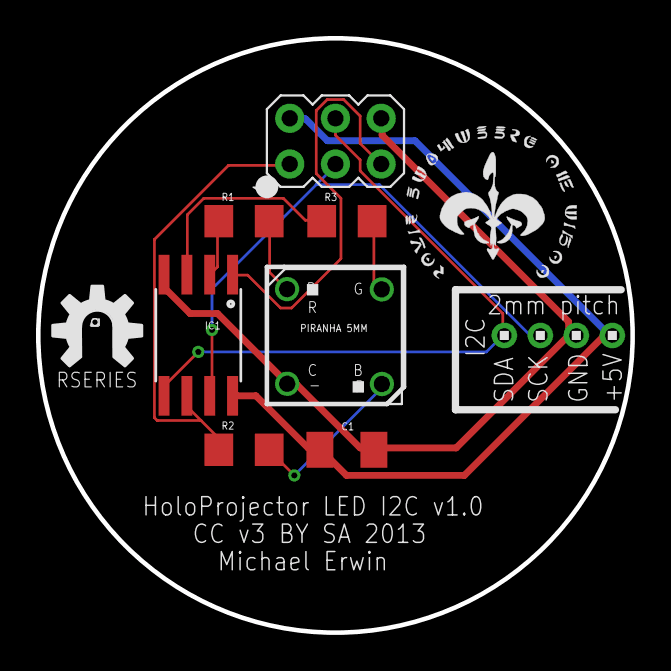
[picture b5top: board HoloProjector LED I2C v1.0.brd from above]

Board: 2 copper layers, 33.0 x 33.0 mm, 10 parts (0 on the bottom side), 11 nets.

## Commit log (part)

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2013-05-09 Added logic display sketch for a Rainbowduino and RGB LED matrix.
2013-05-09 Edited wiki page RSeriesI2CAddressAssignments through web user interface.
2013-05-09 tweaked settings to get this looking closer to the Empire reference video.
2013-05-19 WIP GFX library including menu management and registerable callback buttons for r-series controller. Compiles correctly, much of structure there, but needs the controller sketch updated extensively t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
2013-08-07 Tweaked things and added Teeces PSI code (not working)
2013-09-05 Need to repackage inductor on Logic Engine to include GND (duh!)
2013-09-12 added WS2812 LEDs to the Eagle library. Started reworking the FLD board.
2013-09-20 added microSD card holder to the RSeries library and Logic Engine (still unfinished)
2013-09-21 Created wiki page through web user interface.
2013-09-22 Edited wiki page WS2812_LED_Testing through web user interface.
2013-10-12 increased MicroSD gnd pad size to make it more sturdy.
2013-11-01 More work on the graphics lib. Began rewriting the controller sketch, but its not working yet, so not checking that in yet. Having trouble with the dynamic menu system.
2013-11-08 New Wav shield audio sketch, supporting libs and examples with mods, Improved and cleaned up receiver sketch
2013-11-08 Adding jukebox wav shield wrapper lib. missed on last submit.
2013-11-08 Cleanup of shoulder controller sketch
2013-11-08 Well, the nunchuk is still inoperative, but the code is left there for it, just commented out. Its possible my nunchuk is busted in some way, or possibly I have a wierd memory problem. Anyways what's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
2013-11-10 Bugfix: controller sketch would repeatedly send the last command, since it didnt zero it out after sending.
2013-11-10 ignore commands recieved while playing a sound already
2013-11-20 added small round R2 Builders logo and the final trimpots used on the Logic Engine board
2013-11-25 added WS2812B LEDs (the 4-pin variant of the WS2812)
2013-11-26 Lifter controller sketch and supporting library for Adafruit motor shield V2
2013-11-30 cross section of FLD showing parts for assembly
2013-11-30 drawing of Logic Engine AVR board
2013-12-03 image of rear logic LED boards
2013-12-03 image of LED boards in front formation
2013-12-03 Edited wiki page RSeriesLogicEngine through web user interface.
2013-12-05 added basic sketch for the Logic Engine
2014-01-06 image for wiki
2014-01-08 Added final Logic Engine Eagle files. Removed Logics WIP folder (unfinished/incorrect designs).
2014-01-08 Added most recent 'Basic' logic sketch. Supports 'Testpattern Mode', still lacks microSD support (next!).
2014-01-08 revised logic sketch to fix rldMap
2014-01-09 fixed fldMap for final LED board orientation
2014-01-12 fixed prototype FLD bug
2014-01-15 started freeing up RAM to make way for the SD card
2014-01-16 More Logic Engine RAM optimizing. Version 7 leaves 830 bytes free
2014-01-16 cleaned up code a little
2014-01-22 further ensmallening
2014-03-10 Logic Engine sketch with support for Teeces PSI
2014-03-18 Edited wiki page RSeriesLogicEngine through web user interface. Started to flesh out the assembly guide.
2014-03-19 v002 has easily adjustable endpoints
2014-03-20 added some photos to clarify Logic Engine assembly
2014-03-20 added rear bezel image
2014-03-20 added diagram for connecting Teeces PSI
2014-03-25 adjusted pad size of microSD holder
2014-03-31 photo of assembled RLD bowed
2014-03-31 Added notes to prevent RLD from bowing during assembly.
2014-04-03 added mroe RLD assembly photos
2014-04-03 Random sound selection
2014-06-19 added diagram showing FLD hookup
2014-06-25 Droid Wiring & Workshop from DroidCON III
2014-06-25 Arduino Primer by Paul Murphy
2014-08-06 Refining memory usage to get enough free SRAM for the SD card and I2C
2014-08-06 revised LogicEngineBasic8 sketch and added the LedCompact library (runs Teeces PSI using less SRAM)
2014-10-02 numbered assembly pattern
2014-10-02 small version of numbered pattern
2014-11-10 Changed YouTube video link (old version was unviewable in Germany)
2015-01-15 Archive of Padawan sounds converted for use with VS1000 Audio Module
2015-02-26 receiver code updates
2015-02-28 added sketch for droidconuino utility arm cpu arm and 2-3-2 controller, and tx and rx additions for both
2015-03-13 Create gh-pages branch via GitHub

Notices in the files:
parts and their libraries:
SparkFun-DigitalIC: Licensing: CC v3.0 Share-Alike You are welcome to use this library for commercial purposes.
supply0: Copyright (C) 2007, Bob Starr
